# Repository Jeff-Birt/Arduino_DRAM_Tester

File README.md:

# Arduino_DRAM_Tester
Use an Arduino to test retro DRAM chips

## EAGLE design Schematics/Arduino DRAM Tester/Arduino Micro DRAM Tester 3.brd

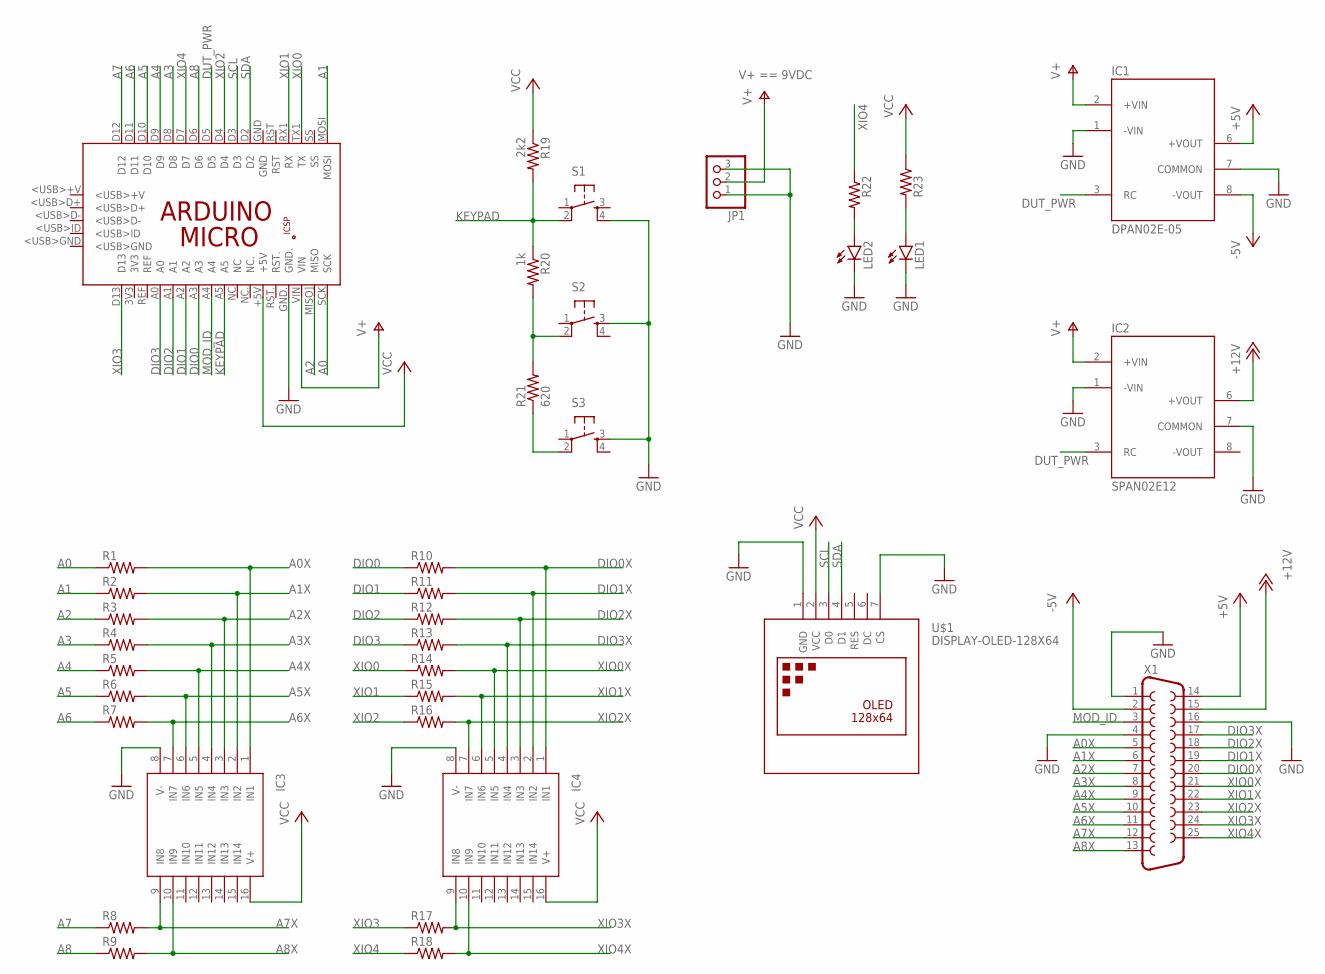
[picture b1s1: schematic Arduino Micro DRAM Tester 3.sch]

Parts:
IC1: DPAN02E-05; SIP7
IC2: SPAN02E12; SIP7
IC3, IC4: SP720; DIL16
JP1: PINHD-1X3/90; 1X03/90
LED1, LED2: LED5MM
PCB1: ARDUINO_MICRO
R1, R2, R3, R4, R5, R6, R7, R8, R9, R10, R11, R12, R13, R14, R15, R16, R17, R18, R22, R23: R-US_0204/7; 0204/7
R19: 2k2; 0204/7
R20: 1k; 0204/7
R21: 620; 0204/7
S1, S2, S3: TAC_SWITCHPTH; TACTILE-PTH
U$1: DISPLAY-OLED-128X64
X1: F25D

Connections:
+5V: IC1.6 (+VOUT), X1.14
+12V: IC2.6 (+VOUT), X1.15
-5V: IC1.8 (-VOUT), X1.2
A0: PCB1.SCK, R1.1
A0X: IC3.1 (IN1), R1.2, X1.5
A1: PCB1.MOSI, R2.1
A1X: IC3.2 (IN2), R2.2, X1.6
A2: PCB1.MISO] (MISO), R3.1
A2X: IC3.3 (IN3), R3.2, X1.7
A3: PCB1.D8, R4.1
A3X: IC3.4 (IN4), R4.2, X1.8
A4: PCB1.D9, R5.1
A4X: IC3.5 (IN5), R5.2, X1.9
A5: PCB1.D10, R6.1
A5X: IC3.6 (IN6), R6.2, X1.10
A6: PCB1.D11, R7.1
A6X: IC3.7 (IN7), R7.2, X1.11
A7: PCB1.D12, R8.1
A7X: IC3.9 (IN8), R8.2, X1.12
A8: PCB1.D6, R9.1
A8X: IC3.10 (IN9), R9.2, X1.13
DIO0: PCB1.A3, R10.1
DIO0X: IC4.1 (IN1), R10.2, X1.20
DIO1: PCB1.A2, R11.1
DIO1X: IC4.2 (IN2), R11.2, X1.19
DIO2: PCB1.A1, R12.1
DIO2X: IC4.3 (IN3), R12.2, X1.18
DIO3: PCB1.A0, R13.1
DIO3X: IC4.4 (IN4), R13.2, X1.17
DUT_PWR: IC1.3 (RC), IC2.3 (RC), PCB1.D5
GND: IC1.1 (-VIN), IC1.7 (COMMON), IC2.1 (-VIN), IC2.7 (COMMON), IC3.8 (V-), IC4.8 (V-), JP1.1, JP1.3, LED1.K (C), LED2.K (C), PCB1.GND., S1.4, S2.3, S3.3, U$1.1 (GND), U$1.7 (CS), X1.16
KEYPAD: PCB1.A5, R19.2, R20.1, S1.2
MOD_ID: PCB1.A4, X1.3
unnamed: R20.2, R21.2, S2.2
unnamed: R21.1, S3.2
unnamed: LED1.A, R23.2
unnamed: LED2.A, R22.2
SCL: PCB1.D3, U$1.3 (D0)
SDA: PCB1.D2, U$1.4 (D1)
V+: IC1.2 (+VIN), IC2.2 (+VIN), JP1.2, PCB1.VIN
VCC: IC3.16 (V+), IC4.16 (V+), PCB1.+5V, R19.1, R23.1, U$1.2 (VCC)
XIO0: PCB1.TX1 (TX), R14.1
XIO0X: IC4.5 (IN5), R14.2, X1.21
XIO1: PCB1.RX1 (RX), R15.1
XIO1X: IC4.6 (IN6), R15.2, X1.22
XIO2: PCB1.D4, R16.1
XIO2X: IC4.7 (IN7), R16.2, X1.23
XIO3: PCB1.D13, R17.1
XIO3X: IC4.9 (IN8), R17.2, X1.24
XIO4: PCB1.D7, R18.1, R22.1
XIO4X: IC4.10 (IN9), R18.2, X1.25

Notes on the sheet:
V+ == 9VDC

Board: 2 copper layers, 36 parts (0 on the bottom side), 51 nets, no tracks yet.

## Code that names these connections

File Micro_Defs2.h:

#pragma once

//                      Ard      4116		4164       41256		4464
//PORTB bit             Prt Pin  Func PIN	Func Pin   Func PIN		Func PIN
//  RXLED               PB0 
#define A0TOA6  0xFE // PB1 17	 A0   05	A0   05		A0   05		A0   14
//                      PB2 18	 A1   07	A1   07		A1   07		A1   13
//                      PB3 16	 A2   06	A2   06		A2   06		A2   12
//                      PB4 30	 A3   12	A3   12		A3   12		A3   11
//                      PB5 31	 A4   11	A4   11		A4   11		A4   08
//                      PB6 32	 A5   10	A5   10		A5   10		A5   07
//                      PB7 33	 A6   13	A6   13		A6   13		A6   06


//                      Ard      4116		4164       41256		4464
//PORTC bit             Prt Pin  Func Pin   Func PIN	Func PIN	Func PIN
//                      PC0
//                      PC1
//                      PC2
//                      PC3
//                      PC4
//                      PC5
#define DUT_PWR 0x40 // PC6 27
#define WE      0x80 // PC7 01	 WE   03	WE   03		WE   03		WE   04

//                      Ard      4116		4164       41256		4464
//PORTD bit             Prt Pin  Func Pin   Func PIN	Func PIN	Func PIN
// SDA                  PD0 24   
// SCL                  PD1 25
#define CAS     0x04 // PD2 21   CAS  15	CAS  15		CAS	 15		CAS	 16
#define RAS     0x08 // PD3 20   RAS  04	RAS  04		RAS	 04		RAS	 05
// open              // PD4 
// TXLED                PD5
#define A7TOA8  0xC0 // PC6 34							A7   01
//                      PC7 28							A8   09
#define A7      0xC0 // PC6 34										A7   10
#define NOTG         // PC7 28										/G   01


//                      Ard      4116		4164		41256		4464
//PORTE bit             Prt Pin  Func Pin   Func PIN	Func PIN	Func PIN
//					    PE0
//					    PE1
//					    PE2
//					    PE3
//					    PE4
//						PE5
#define GRN_LED	0x40 // PE6 29
//					    PE7


//                      Ard      4116		4164       41256		4464
//PORTF bits            Prt Pin  Func Pin   Func PIN	Func PIN	Func PIN
#define KEYPAD  0x01 // PF0 09	(A5) 
#define MOD_ID  0x02 // PF1 08	(A4)
//              0x04    PF2
//              0x08    PF3
#define DIN     0x10 // PF4 07	 DIN  02	DIN  02		DIN  02		DQ1	02
#define DOUT    0x20 // PF5 06	 DOUT 14	DOUT 14		DOUT 14		DQ2	03
#define DIO0    0x10 // PF4 07	 DIN  02	DIN  02		DIN  02		DQ1	02
#define DIO1    0x20 // PF5 06	 DOUT 14	DOUT 14		DOUT 14		DQ2	03
#define DIO2    0x40 // P65 05										DQ3	15
#define DIO3    0x80 // PF7 04										DQ4	17




// to set pins to HIZ set DDRx bits to zero and set corresponding PORTx pin low
void initTest()
{
	DDRB = DDRB | A0TOA6;			// outputs
	DDRC = DDRC | DUT_PWR | WE;		// outputs
	DDRD = DDRD | A7TOA8 | CAS | RAS; // outputs
	DDRE = DDRE | GRN_LED;			// outputs
	DDRF = DDRF | DIN;				// output
	DDRF = DDRF & ~DOUT;			// input

	PORTC = PORTC & ~DUT_PWR;		// turn ON +5V to DUT 
	PORTC = PORTC | WE;				// WE HIGH (off)
	PORTD = PORTD | RAS | CAS;		// set HIGH (off)
	PORTE = PORTE & ~GRN_LED;		// turn off LED	
}

// For HIZ set DDRx bits to inputs (zero) and set corresponding PORTx pins low
void initStandby()
{
	DDRB = DDRB & ~A0TOA6;			// inputs
	DDRC = DDRC & ~WE;				// inputs
	DDRD = DDRD & ~(A7TOA8 | RAS | CAS); // inputs
	DDRE = DDRE | GRN_LED;			// output even in init
	DDRF = DDRF & ~(DIN | DOUT);	// inputs

	PORTB = PORTB & ~A0TOA6;		// set low
	PORTC = PORTC & ~WE;			// set low
	PORTD = PORTD & ~(A7TOA8 | RAS | CAS);	// set low
	PORTF = PORTF | DUT_PWR;		// turn OFF +5V to DUT
	PORTF = PORTF & ~(DIN | DOUT);	// set low
}

// set Data IN pin of DRAM
//inline void setDIN(byte pattern, byte bitMask)
inline void setDIN(bool state)
{
	PORTF = (PORTF & ~DIN) | (state ? DIN : 0); // clear DIN bit, conditinally set
}

// set column address, could combine with row as well
inline void setCol(int col)
{
	PORTB = (byte)(col << 1);   // Write out COL address
	PORTD = (PORTD & ~A7TOA8) | ((col & 0x180) >> 1); //
}

inline void setRow(int row)
{
	PORTB = (byte)(row << 1);    // Write out ROW address
	PORTD = (PORTD & ~A7TOA8) | ((row & 0x180) >> 1); // 
}

// set Column Address Select HIGH (off)
inline void resetCAS()
{
	PORTD = PORTD | CAS;  // Set CAS HIGH
}

// set Column Address Select LOW (on)
inline void setCAS()
{
	PORTD = PORTD & ~CAS; // Set CAS LOW
}

// set Row Address Select HIGH (off)
inline void resetRAS()
{
	PORTD = PORTD | RAS;  // Set RAS HIGH
}

// set Row Address Select LOW (on)
inline void setRAS()
{
	PORTD = PORTD & ~RAS; // set RAS low
}

// set Write Enable HIGH (off)
inline void resetWE()
{
	PORTC = PORTC | WE;   // Set WE high to complete write
}

// set Write Enable LOW (on)
inline void setWE()
{
	PORTC = PORTC & ~WE;  // Set WE low for write
}

// read bit state from DRAM DOUT pin
inline bool readDOUT()
{
	return ((PINF & DOUT) != 0);
}

// refresh row to maintain DRAM data
inline void refreshRow(int row)
{
	PORTB = (byte)(row << 1);    // Write out ROW address
	PORTD = (PORTD & ~A7TOA8) | ((row & 0x180) >> 1); // 
	PORTD = PORTD & ~RAS; // set RAS low
	PORTD = PORTD | RAS;  // set RAS high
}

// turn LED off
inline void ledOFF()
{
	PORTE = PORTE & ~GRN_LED; // turn off grn LED
}

// turn LED on
inline void ledON()
{
	PORTE = PORTE | GRN_LED; // turn off grn LED
}

// toggle LED state
inline void ledToggle()
{
	PORTE = PORTE ^ GRN_LED; // toggle grn LED
}

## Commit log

2019-09-19 Add files via upload
    Initial commit of code
2019-09-21 Fixed some comments and added schematics
2019-10-04 Added def for Nano and Micro. Tested on Mega and Micro. Will add display next
2019-10-09 Commit before OLED UI update
2019-10-10 OLED UI now working
2019-10-11 Working OLED UI and power up of DC-DC converter(s)
2019-10-17 Redefined port/pin layout to allow for future expansion.
2019-10-23 Added schematic for V3B for Arduino Micro. This is made to fit a readily available enclosure.

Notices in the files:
parts and their libraries:
SparkFun-Electromechanical: Licensing: CC v3.0 Share-Alike You are welcome to use this library for commercial purposes.
diy-modules: Released under the Creative Commons Attribution 4.0 International License: http://creativecommons.org/licenses/by/4.0
